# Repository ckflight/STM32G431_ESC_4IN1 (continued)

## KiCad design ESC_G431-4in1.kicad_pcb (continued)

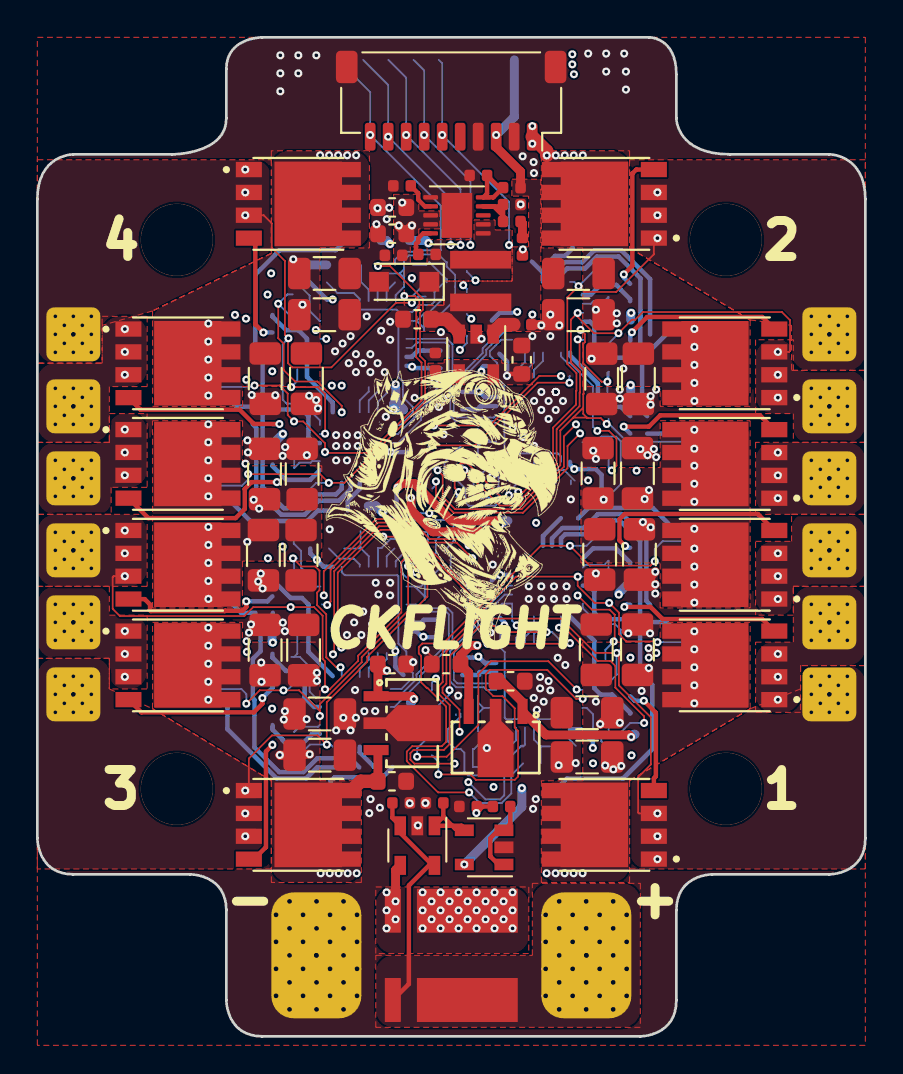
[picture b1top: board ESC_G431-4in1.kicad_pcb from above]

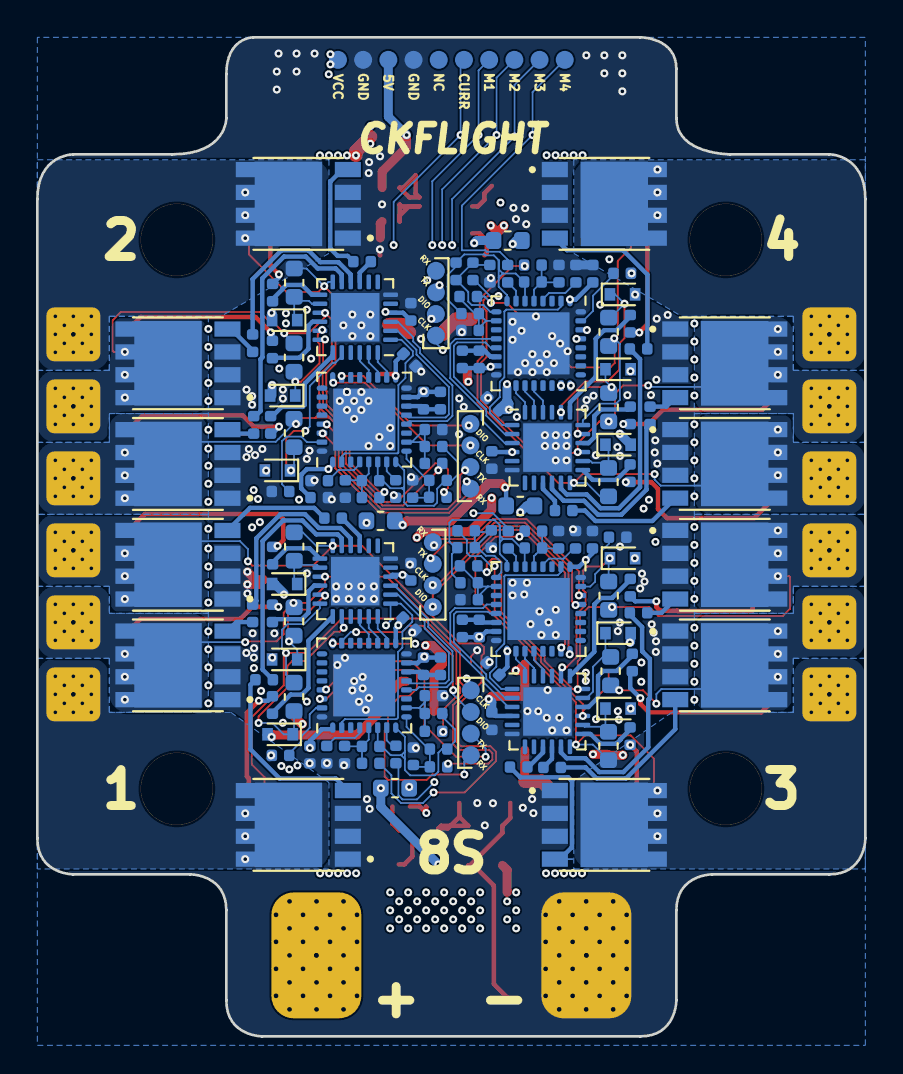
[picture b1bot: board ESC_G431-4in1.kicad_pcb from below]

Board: 4 copper layers, 46.0 x 55.5 mm, 222 parts (149 on the bottom side), 168 nets.

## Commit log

2025-08-04 Pcb design init commit
2025-08-04 ESC 3d model correction and logo
2025-08-04 Pictures of the 3D view is added to READMD
